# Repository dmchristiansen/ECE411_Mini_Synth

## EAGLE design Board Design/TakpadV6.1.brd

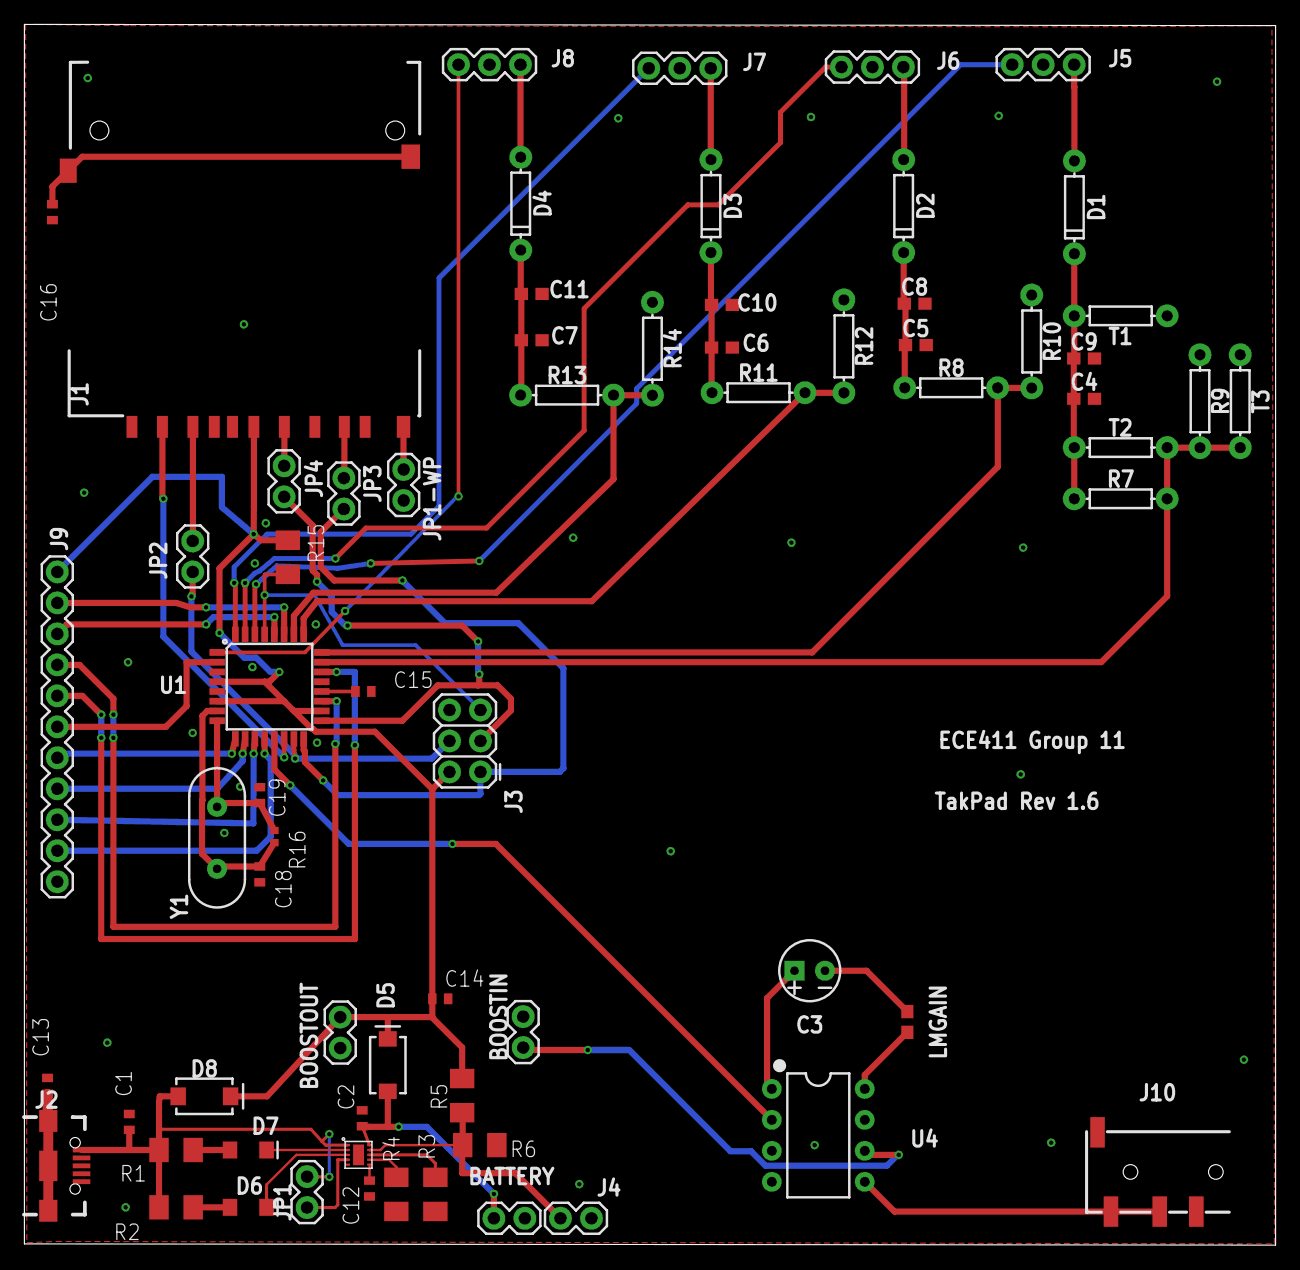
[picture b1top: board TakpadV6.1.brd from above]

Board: 2 copper layers, 102.6 x 100.1 mm, 68 parts (0 on the bottom side), 58 nets.

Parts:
BATTERY: 1X02
BOOSTIN: 1X02
BOOSTOUT: 1X02
C1, C2, C14: 10u; C0402
C3: 10uF; CPOL-RADIAL-2.5MM-5MM-KIT
C4, C5, C6, C7: 47pF; 0603
C8, C9, C10, C11: 1uF; 0603
C12, C13, C15, C16: 0.1u; C0402
C18, C19: 22pF; C0402
D1, D2, D3, D4: 200mA/100V/1V; DIODE-1N4148
D5, D8: 2A/40V/360mV; SMA-DIODE
D6: RED; LED-1206
D7: GREEN; LED-1206
J1: SD_CARD_SOCKET; SD
J2: USB-B-MICRO-SMD_RED_PASTE
J3: AVR_SPI_PROG_3X2PTH; 2X3
J4: 1X02
J5, J6, J7, J8: 1X03
J9: 1X11
J10: AUDIO_JACK_TRRSSMD_RA; AUDIO_JACK_3.5MM_TRRS_SMD_RA
JP1, JP1-WP, JP2, JP3, JP4: 1X02
LMGAIN: 1; 0603
R1, R2: 1.5k; M1206
R3: 13.3k; M1206
R4: 1.87k; M1206
R5, R6, R15: 10k; M1206
R7, R8, R11, R13: 470k; AXIAL-0.3
R9, R10, R12, R14: 150k; AXIAL-0.3
R16: 1M; R0402
T1, T2, T3: 0; AXIAL-0.3
U1: ATMEGA328P_TQFP; TQFP32-08
U4: LM386N; DIP08
U$1: AAT3693; IDH-AA-T1
Y1: 20MHz; HC49US

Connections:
ADC4: J9.2, U1.27
ADC5: J9.3, U1.28
ADC6: J9.4, U1.19
ADC7: J9.5, U1.22
AREF: C15.1, U1.20
AUDIOINPUT: U1.13, U4.2
AUDIOOUT: J10.RING1, J10.TIP, U4.5
BAT: BATTERY.2, C2.2, D5.A, U$1.BAT
CD/DAT3: J1.1, U1.14
CLK: J1.5, JP4.1
CMD: J1.2, JP2.2
CT: C12.1, U$1.CT
DAT0: J1.7, JP3.1
EN: JP1.1, U$1.EN
GND: BATTERY.1, BOOSTIN.2, BOOSTOUT.2, C1.2, C2.1, C4.2, C5.2, C6.2, C7.2, C8.2, C9.2, C10.2, C11.2, C12.2, C13.2, C14.2, C15.2, C16.2, C18.1, C19.2, J1.3, J1.6, J2.GND, J3.6, J4.2, J5.2, J6.2, J7.2, J8.2, J9.11, J10.EARTH, J10.RING2, JP1-WP.2, R3.1, R4.1, R6.1, R9.P$1, R10.P$1, R12.P$1, R14.P$1, T1.P$1, T3.P$1, U1.3, U1.5, U1.21, U4.3, U4.4, U$1.EP, U$1.GND
ISET: R4.2, U$1.ISET
MISO: J3.1, JP3.2, U1.16
MOSI: J3.4, JP2.1, U1.15
unnamed: C13.1, J2.SHIELD1, J2.SHIELD2, J2.SHIELD3
unnamed: C3.1, U4.1
unnamed: C3.2, LMGAIN.2
unnamed: LMGAIN.1, U4.8
unnamed: C16.1, J1.SH@1, J1.SH@2
PB6: C18.2, R16.2, U1.7, Y1.2
PB7: C19.1, R16.1, U1.8, Y1.1
PD4: J9.6, U1.2
PD5: J9.7, U1.9
PD6: J9.8, U1.10
PD7: J9.9, U1.11
PD8: J9.10, U1.12
RST: J3.5, R15.2, U1.29
SCK: J3.3, JP4.2, U1.17
SENS1LED: J5.1, U1.30
SENS2LED: J6.1, U1.31
SENS3LED: J7.1, U1.32
SENS4LED: J8.1, U1.1
SENSOR1: D1.A, J5.3
SENSOR1IN: C4.1, C9.1, D1.C, R7.P$1, T1.P$2, T2.P$1
SENSOR1OUT: R7.P$2, R9.P$2, T2.P$2, T3.P$2, U1.23
SENSOR2: D2.A, J6.3
SENSOR2IN: C5.1, C8.1, D2.C, R8.P$1
SENSOR2OUT: R8.P$2, R10.P$2, U1.24
SENSOR3: D3.A, J7.3
SENSOR3IN: C6.1, C10.1, D3.C, R11.P$1
SENSOR3OUT: R11.P$2, R12.P$2, U1.25
SENSOR4: D4.A, J8.3
SENSOR4IN: C7.1, C11.1, D4.C, R13.P$1
SENSOR4OUT: R13.P$2, R14.P$2, U1.26
STAT1: D7.C, U$1.STAT1
STAT1LED: D7.A, R1.1
STAT2: D6.C, U$1.STAT2
STAT2LED: D6.A, R2.1
TEMPSENSE: J4.1, R5.1, R6.2, U$1.TS
TERM: R3.2, U$1.TERM
UPCONVERTERINPUT: BOOSTIN.1, U4.6
V+: BOOSTOUT.1, C14.1, D5.C, D8.C, J1.4, J3.2, J9.1, R5.2, R15.1, U1.4, U1.6, U1.18
VIN: C1.1, D8.A, J2.VBUS, JP1.2, R1.2, R2.2, U$1.VIN
WP: J1.WP, JP1-WP.1

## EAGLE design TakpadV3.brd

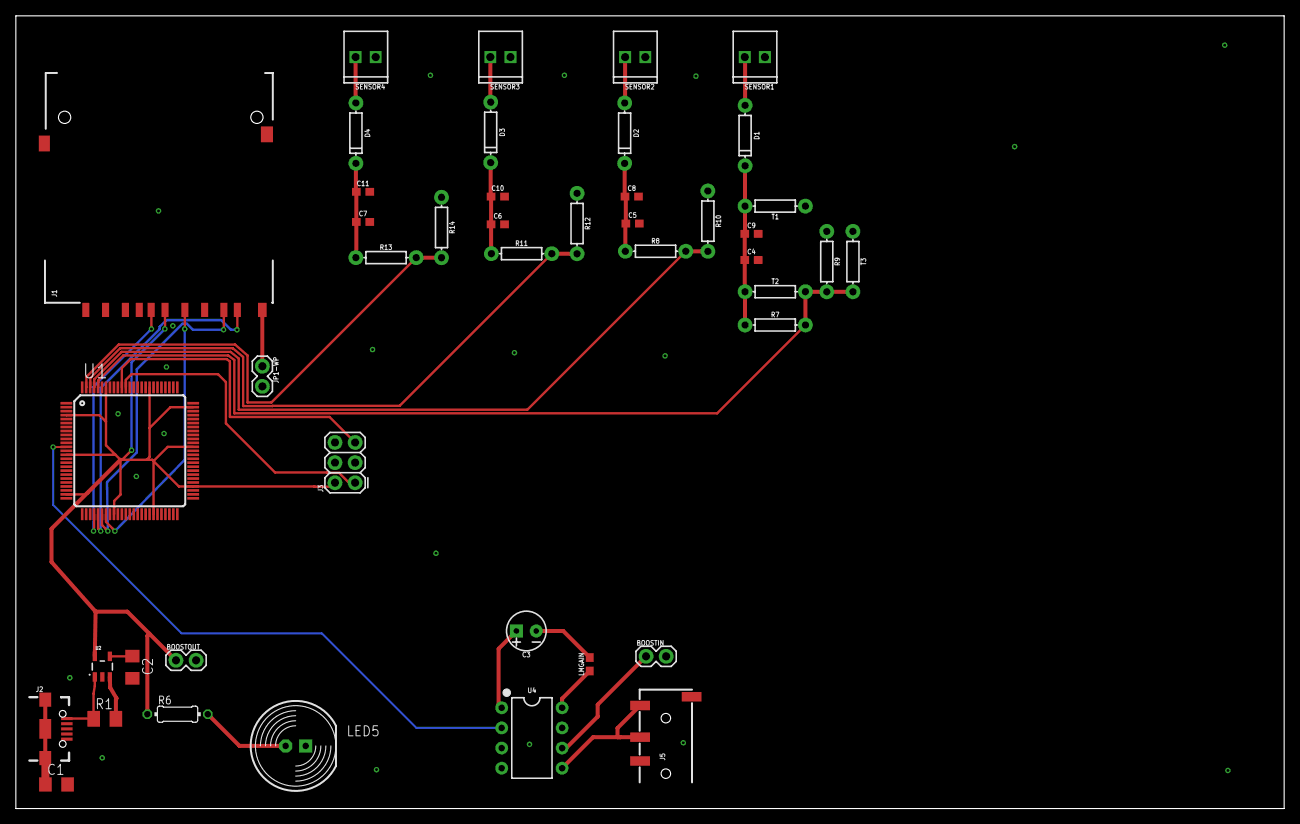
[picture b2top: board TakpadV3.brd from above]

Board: 2 copper layers, 160.0 x 100.0 mm, 44 parts (0 on the bottom side), 32 nets.

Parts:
BOOSTIN: 1X02
BOOSTOUT: 1X02
C1: 100n; C1206
C2: 470p; C1206
C3: 10uF; CPOL-RADIAL-2.5MM-5MM-KIT
C4, C5, C6, C7: 47pF; 0603
C8, C9, C10, C11: 1uF; 0603
D1, D2, D3, D4: 200mA/100V/1V; DIODE-1N4148
J1: SD_CARD_SOCKET; SD
J2: USB-B-MICRO-SMD
J3: AVR_SPI_PROG_3X2PTH; 2X3
J5: AUDIO_JACK_TRRSSMD_RA; AUDIO_JACK_3.5MM_TRRS_SMD_RA
JP1-WP: 1X02
LED5: LED10MM
LMGAIN: 1; 0603
R1: 10k; M1206
R6: 330; 0204/7
R7, R8, R11, R13: 470k; AXIAL-0.3
R9, R10, R12, R14: 150k; AXIAL-0.3
SENSOR1, SENSOR2, SENSOR3, SENSOR4: 1X02_2.54_SCREWTERM
T1, T2, T3: 0; AXIAL-0.3
U1: ATXMEGA128A1U-AU; TQFP-100A-100
U2: 3.3V/150mA; SOT23-5
U4: LM386N; DIP08

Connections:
AUDIOINPUT: U1.12, U4.2
AUDIOOUT: J5.RING1, J5.TIP, U4.5
BP: C2.1, U2.4
CD: J1.CD, U1.29
CLK: J1.5, U1.32
DAT0: J1.7, U1.31
DAT1: J1.8, U1.30
EN: R1.2, U2.3
GND: BOOSTIN.2, BOOSTOUT.2, C1.2, C2.2, C4.2, C5.2, C6.2, C7.2, C8.2, C9.2, C10.2, C11.2, J1.3, J1.6, J2.GND, J3.6, J5.EARTH, J5.RING2, JP1-WP.2, LED5.K, R9.P$1, R10.P$1, R12.P$1, R14.P$1, SENSOR1.P2, SENSOR2.P2, SENSOR3.P2, SENSOR4.P2, T1.P$1, T3.P$1, U1.3, U1.13, U1.23, U1.33, U1.43, U1.53, U1.63, U1.73, U1.84, U1.93, U2.2, U4.3, U4.4
LED: LED5.A, R6.2
MISO: J3.1, U1.89
unnamed: C3.1, U4.1
unnamed: C3.2, LMGAIN.2
unnamed: LMGAIN.1, U4.8
RST: J3.5, U1.90
SENSOR1: D1.A, SENSOR1.P1
SENSOR1IN: C4.1, C9.1, D1.C, R7.P$1, T1.P$2, T2.P$1
SENSOR1OUT: R7.P$2, R9.P$2, T2.P$2, T3.P$2, U1.96
SENSOR2: D2.A, SENSOR2.P1
SENSOR2IN: C5.1, C8.1, D2.C, R8.P$1
SENSOR2OUT: R8.P$2, R10.P$2, U1.97
SENSOR3: D3.A, SENSOR3.P1
SENSOR3IN: C6.1, C10.1, D3.C, R11.P$1
SENSOR3OUT: R11.P$2, R12.P$2, U1.98
SENSOR4: D4.A, SENSOR4.P1
SENSOR4IN: C7.1, C11.1, D4.C, R13.P$1
SENSOROUT4: R13.P$2, R14.P$2, U1.99
SHIELD: C1.1, J2.SHIELD1, J2.SHIELD2, J2.SHIELD3
UPCONVERTERINPUT: BOOSTIN.1, U4.6
V+: BOOSTOUT.1, J1.4, J3.2, R6.1, U1.4, U1.14, U1.24, U1.34, U1.44, U1.54, U1.64, U1.74, U1.83, U1.94, U2.5
VIN: J2.VBUS, R1.1, U2.1
WP: J1.WP, JP1-WP.1

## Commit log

2017-10-22 testing squash and merge
2017-10-23 Revert " testing squash and merge"
    This reverts commit 89208da5db01c362755d267b8bf134866aae7710.
2017-11-02 Delete Sound Board V2.zip
    removing file for rename
2017-11-02 Add files via upload
    renamed file for schematic
2017-11-06 Create 10-03-17
2017-11-06 Create 10-09-17
2017-11-06 Create 10-11-17
2017-11-06 Create 10-27-17
2017-11-06 Create 11-03-17
2017-11-08 Create Pinout
2017-11-08 Preliminary block diagram of "TAKPAD"
2017-11-08 Added Top_level.xml
2017-11-08 Added Top_level.jpg
2017-11-08 Added Top_level.png
2017-11-08 Added Input_filter
2017-11-08 Add files via upload
    Block Diagram of Charging Circuit
2017-11-08 Added Input_filter.png
2017-11-08 Add files via upload
    Audio Amplifier Stage Block Diagram
2017-11-09 Add files via upload
    -Sensor Inputs Added
    -Audio Output Added
    -Initial Board Layout Created
2017-11-10 Add files via upload
    Initial Charging Circuit Design
2017-11-10 Create 328p Pinout
2017-11-11 Added needed connections
2017-11-14 Add files via upload
    Caps should be 22pF
2017-11-14 Add files via upload
    Updated processor, added charging schematic
2017-11-15 fixed polling loop
2017-11-15 Add files via upload
    Board layout completed
    Added pinout for unused pins
    Added LEDout to sensor connectors
2017-11-15 Add files via upload
    Minor Changes
2017-11-15 Add files via upload
    added test points to voltage points of interest. Caps to input voltages, cap on output of lm386, smd resistors on inputs
2017-11-16 Add files via upload
    TO DO LIST:
    MAJOR - 0.1uF caps by voltage pins - done (some of these are 1uF, is this the right value?)
    Label pinouts, (not really sure what I am supposed to label)
    change a few font sizes
    some routing
    some TP placement
2017-11-16 Add files via upload
    nearly done hope this works, cross fingers
2017-11-16 added tc_init, wavetable
2017-11-17 Added wavetable and untested interrupt routine
2017-11-18 It produces terrible noises now
2017-11-20 added LFO but it still sounds bad
2017-11-21 Fixed note_count behaivor, tidied code
2017-11-22 about to change some stuff
2017-11-22 Changed wavetables, worked on ADSR
2017-11-25 gaahhhh
2017-11-25 ADSR components in place
2017-11-25 Implemented ADSR envelope
2017-11-25 updated to do
2017-11-30 Add files via upload
    Test Plan documentation for ECE 411 HW 7
2017-12-02 minor updates
2017-12-05 added kicks, adsr frequency
2017-12-07 fixed multi-note triggering & note overlap
2017-12-07 tidying repo
2017-12-07 added datasheets

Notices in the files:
parts and their libraries:
SparkFun-Connectors: Licensing: Creative Commons ShareAlike 4.0 International - https://creativecommons.org/licenses/by-sa/4.0
